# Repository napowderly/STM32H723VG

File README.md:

# stm32h723vg

Wooohooo a new package!

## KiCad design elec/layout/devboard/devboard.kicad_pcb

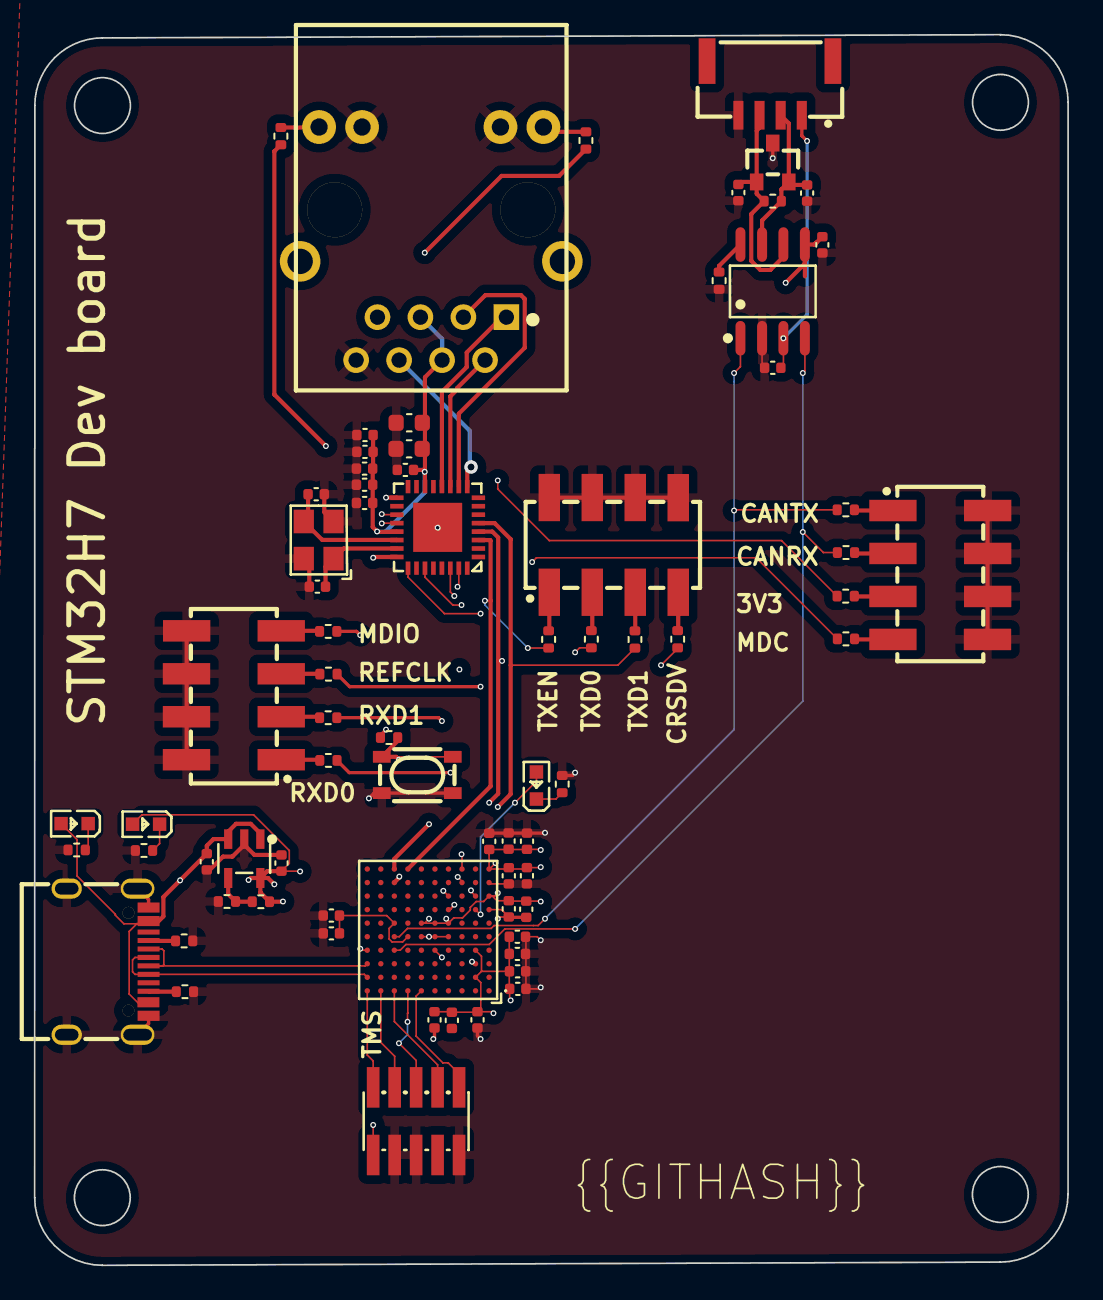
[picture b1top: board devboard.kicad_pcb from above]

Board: 6 copper layers, 61.1 x 72.8 mm, 73 parts (0 on the bottom side), 55 nets.

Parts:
C1, C2: 6.3V 2.2uF X5R ±20% 0402 Multilayer Ceramic Capac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; C0402
C3: 10V 4.7uF X5R ±20% 0402 Multilayer Ceramic Capaci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; C0402
C4, C5, C6, C7, C8, C9, C10, C11, C12, C14, C16, C19, C23, C29, C30: 16V 100nF X7R ±10% 0402 Multilayer Ceramic Capaci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; C0402
C13, C15, C18, C22, C27, C28: 25V 1uF X5R ±10% 0402 Multilayer Ceramic Capacito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; C0402
C17, C21: 10V 10uF X5R ±10% 0603 Multilayer Ceramic Capacit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; C0603
C20, C24: 50V 10nF X7R ±10% 0402 Multilayer Ceramic Capacit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; C0402
C25, C26: 50V 12pF C0G ±5% 0402 Multilayer Ceramic Capacito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; C0402
C31, C32: 25V 47nF X7R ±10% 0402 Multilayer Ceramic Capacit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; C0402
J1: CONN-SMD_4P-P1.25_SM04B-GHS-TB-LF-SN
LED1, LED2, LED3: LED0603-RD
R1, R8: 62.5mW Thick Film Resistors 50V ±100ppm/℃ ±1% 10k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; R0402
R2, R3: 62.5mW Thick Film Resistors 50V ±100ppm/℃ ±1% 4.7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; R0402
R4, R5, R13, R14, R15, R16, R17, R18, R19, R20, R21, R22, R23, R24: 62.5mW Thick Film Resistors 50V ±100ppm/℃ ±1% 1kΩ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; R0402
R6: 62.5mW Thick Film Resistors 50V ±100ppm/℃ ±1% 11.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; R0402
R7: 62.5mW Thick Film Resistors 50V ±100ppm/℃ ±1% 6.2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; R0402
R9: 62.5mW Thick Film Resistors 50V ±100ppm/℃ ±1% 120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; R0402
R10: 62.5mW Thick Film Resistors 50V ±100ppm/℃ ±1% 464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; R0402
R11: 62.5mW Thick Film Resistors 50V ±100ppm/℃ ±1% 324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; R0402
R12: 62.5mW Thick Film Resistors 50V ±100ppm/℃ ±1% 1.2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; R0402
U1: TFBGA-100_L8.0-W8.0-R10-C10-P0.80-BL
U2: KEY-SMD_4P-L4.2-W3.2-P2.20-LS4.6
U3: USB-C-SMD_KH-TYPE-C-16P
U4: HDR-SMD_10P-P1.27-V-M-R2-C5-LS5.3
U5: VQFN-32_L5.0-W5.0-P0.50-TL-EP2.9
U6: RJ45-TH_HR913550A
U7: OSC-SMD_4P-L3.2-W2.5-BL
U8: SOT-23-5_L3.0-W1.7-P0.95-LS2.8-BL
U9: SOIC-8_L4.9-W3.9-P1.27-LS6.0-BL
U10: SOT-23_L2.9-W1.3-P1.90-LS2.4-BR
U11, U12, U13: HDR-SMD_8P-P2.54-V-M-R2-C4-LS7.4

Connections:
blinky.resistor-cathode: LED3.1, R12.1
boot0: R1.2, U1.D5, U2.1, U2.2
can_interface.transceiver-vcc: R8.1, U9.8
can_saleae.header-_1: R13.2, U11.1
can_saleae.header-_3: R14.2, U11.3
can_saleae.header-_5: R15.2, U11.5
can_saleae.header-_7: R16.2, U11.7
canh: C32.1, J1.2, R9.2, U9.7, U10.2
canl: C31.1, J1.3, R9.1, U9.6, U10.1
cc1: R2.1, U3.A5
cc2: R3.1, U3.B5
crs_dv: R20.1, U1.K3, U5.27
dm: U1.C10, U3.A7, U3.B7
dp: U1.B10, U3.A6, U3.B6
green_led_anode: R4.2, U6.9
input: LED3.2, U1.G2
link_led: R4.1, U5.17
mdc: R16.1, U1.J3, U5.20
mdio: R24.1, U1.D10, U5.19
micro.ic-gnd: C1.2, C2.2, C3.2, C4.2, C5.2, C6.2, C7.2, C8.2, C9.2, C10.2, C11.2, C12.2, C13.2, C14.2, C15.2, C17.2, C18.2, C19.2, C20.2, C21.2, C22.2, C23.2, C24.2, C25.2, C26.2, C27.2, C28.2, C29.2, C30.2, C31.2, C32.2, J1.4, R2.2, R3.2, R7.2, R8.2, R10.2, R11.2, R12.2, U1.C2, U1.E4, U1.E5, U1.E6, U1.G1, U1.J1, U2.3, U2.4, U3.1, U3.2, U3.3, U3.4, U3.A1, U3.A12, U3.B1, U3.B12, U4.3, U4.5, U4.9, U5.33, U6.8, U6.10, U6.11, U7.2, U7.4, U8.2, U9.2, U10.3, U11.2, U11.4, U11.6, U11.8, U12.2, U12.4, U12.6, U12.8, U13.2, U13.4, U13.6, U13.8
micro.ic-vcc: C3.1, C4.1, C5.1, C6.1, C7.1, C8.1, C9.1, C10.1, C11.1, C12.1, C13.1, C14.1, C15.1, C16.2, C17.1, C18.1, C19.1, C20.1, C21.1, C22.1, C23.1, C24.1, C28.1, C29.1, LED2.2, R1.1, R6.1, R15.1, U1.B2, U1.D2, U1.F4, U1.F5, U1.F6, U1.H1, U1.K1, U4.1, U5.14, U5.21, U6.4, U6.5, U8.5, U9.5
micro.ic-vcc-1: C1.1, C2.1, U1.E7, U1.F8
out: R6.2, R7.1, U8.4
phy.ic-vcc: C25.1, U5.23, U7.1
phy.ic-vcc-1: C26.1, U5.22, U7.3
power3v3_led.resistor-cathode: LED2.1, R11.1
power5v_led.resistor-cathode: LED1.1, R10.1
rdm: U5.9, U6.6
rdp: U5.10, U6.3
ref_clk: R23.1, U1.H2, U5.25
reset: U1.A6, U4.10
rmii_saleae_1.header-_1: R17.2, U12.1
rmii_saleae_1.header-_3: R18.2, U12.3
rmii_saleae_1.header-_5: R19.2, U12.5
rmii_saleae_1.header-_7: R20.2, U12.7
rmii_saleae_2.header-_1: R21.2, U13.1
rmii_saleae_2.header-_3: R22.2, U13.3
rmii_saleae_2.header-_5: R23.2, U13.5
rmii_saleae_2.header-_7: R24.2, U13.7
rx: R14.1, U1.D8, U9.4
rxd0: R21.1, U1.G4, U5.30
rxd1: R22.1, U1.H4, U5.31
speed_led: R5.1, U5.24
tck: U1.A9, U4.4
tdi: U1.A8, U4.8
tdm: U5.11, U6.2
tdo: U1.A7, U4.6
tdp: U5.12, U6.1
tms: U1.A10, U4.2
tx: R13.1, U1.E8, U9.1
txd0: R18.1, U1.K8, U5.4
txd1: R19.1, U1.J8, U5.5
txen: R17.1, U1.K7, U5.3
usbc-vcc: C27.1, C30.1, J1.1, LED1.2, U3.A4, U3.A9, U3.B4, U3.B9, U8.1, U8.3, U9.3
yellow_led_anode: R5.2, U6.12

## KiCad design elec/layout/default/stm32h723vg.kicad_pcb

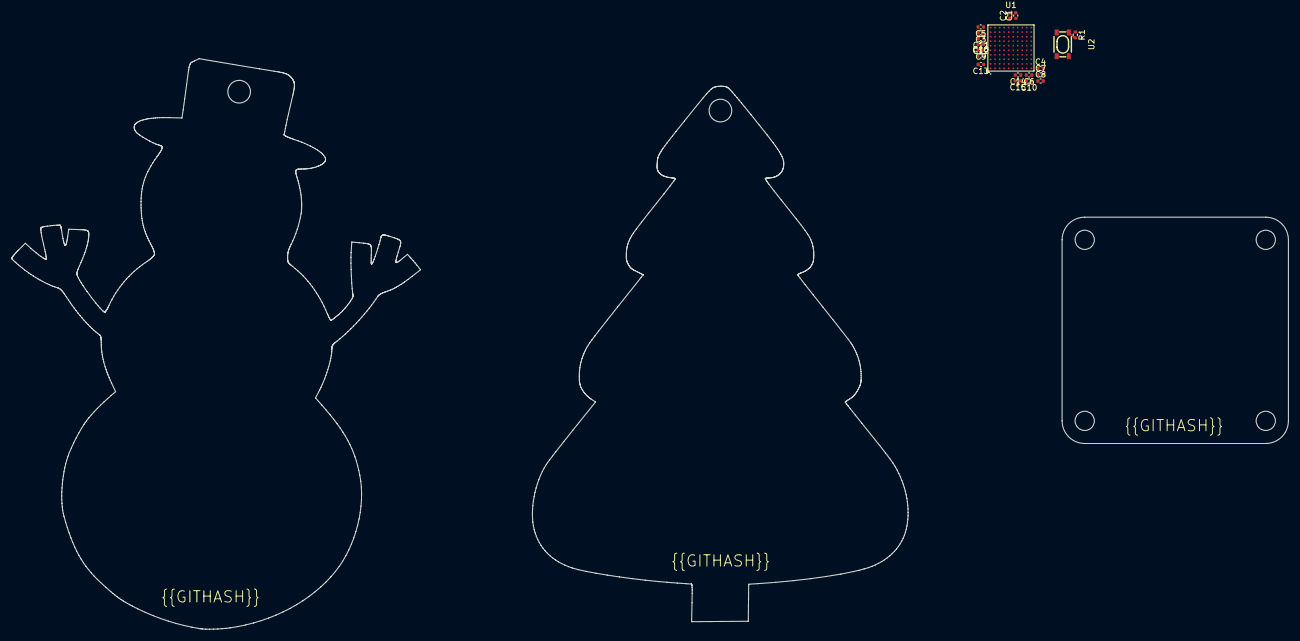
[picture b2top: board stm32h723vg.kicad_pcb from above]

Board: 2 copper layers, 19 parts (0 on the bottom side), 8 nets.

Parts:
C1, C2: 6.3V 2.2uF X5R ±20% 0402 Multilayer Ceramic Capac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; C0402
C3: 10V 4.7uF X5R ±20% 0402 Multilayer Ceramic Capaci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; C0402
C4, C5, C6, C7, C8, C9, C10, C11, C12, C14, C16: 16V 100nF X7R ±10% 0402 Multilayer Ceramic Capaci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; C0402
C13, C15: 25V 1uF X5R ±10% 0402 Multilayer Ceramic Capacito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; C0402
R1: 62.5mW Thick Film Resistors 50V ±100ppm/℃ ±1% 10k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; R0402
U1: TFBGA-100_L8.0-W8.0-R10-C10-P0.80-BL
U2: KEY-SMD_4P-L4.2-W3.2-P2.20-LS4.6

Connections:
boot0: R1.2, U1.D5, U2.1, U2.2
gnd: U2.3, U2.4
ic-gnd: C1.2, C2.2, C3.2, C4.2, C5.2, C6.2, C7.2, C8.2, C9.2, C10.2, C11.2, C12.2, C13.2, U1.C2, U1.E4, U1.E5, U1.E6, U1.J1
ic-gnd-2: C14.2, C15.2, U1.G1
ic-vcc: C3.1, C4.1, C5.1, C6.1, C7.1, C8.1, C9.1, C10.1, C11.1, C12.1, C16.2, U1.D2, U1.F4, U1.F5, U1.K1
ic-vcc-2: C1.1, C2.1, U1.E7, U1.F8
ic-vcc-3: C14.1, C15.1, U1.H1
ic-vcc-5: C13.1, U1.B2

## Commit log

2024-04-22 Configure project
2024-04-30 dev board layout complete
